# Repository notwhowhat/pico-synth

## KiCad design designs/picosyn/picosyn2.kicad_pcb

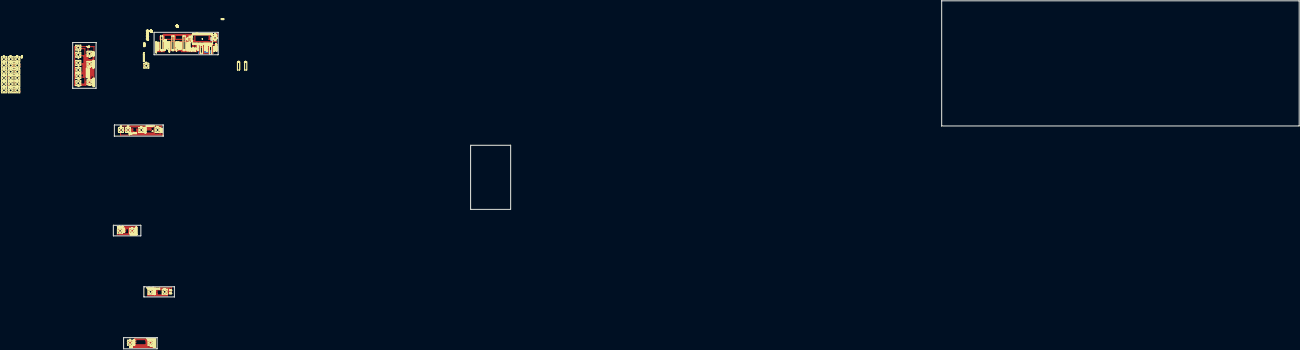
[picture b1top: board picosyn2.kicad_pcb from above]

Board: 2 copper layers, 170 parts (0 on the bottom side), 190 nets.

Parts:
C1: 100 nF; CP_Radial_D5.0mm_P2.50mm
C2: 47 µF; CP_Radial_D5.0mm_P2.50mm
C3, C4, C5, C6, C7, C8, C9: C; CP_Radial_D5.0mm_P2.50mm
D1: 1N4148; D_DO-35_SOD27_P7.62mm_Horizontal
D2, D3, D4, D5, D19, D20, D21, D22, D23, D24, D25, D26, D27, D28, D29, D30, D31, D32, D33, D34, D35, D36, D37, D38, D39, D40, D41, D43, D44, D45, D46, D47, D48, D49, D50, D51: LED; LED_D3.0mm
J3, J6, J9, J11, J15, J31, J32, J34, J35: Conn_01x02_Pin; PinHeader_1x02_P2.54mm_Vertical
J4: BUTTONS_A; PinHeader_1x09_P2.54mm_Vertical
J5: LEDS_A; PinHeader_1x10_P2.54mm_Vertical
J7: BUTTONS_B; PinHeader_1x04_P2.54mm_Vertical
J8, J27: LEDS_B; PinHeader_1x07_P2.54mm_Vertical
J10, J24: LEDS_C; PinSocket_1x06_P2.54mm_Vertical
J12: BUTTONS_C; PinHeader_1x02_P2.54mm_Vertical
J13: BUTTONS_D; PinHeader_1x02_P2.54mm_Vertical
J14: LEDS_D; PinSocket_1x05_P2.54mm_Vertical
J16, J22: BUTTONS_E; PinHeader_1x02_P2.54mm_Vertical
J17, J28: LEDS_E; PinHeader_1x07_P2.54mm_Vertical
J18: BUTTONS_A; PinSocket_1x09_P2.54mm_Vertical
J19: BUTTONS_D; PinSocket_1x02_P2.54mm_Vertical
J20: BUTTONS_C; PinSocket_1x02_P2.54mm_Vertical
J21: BUTTONS_B; PinSocket_1x04_P2.54mm_Vertical
J23: LEDS_A; PinSocket_1x10_P2.54mm_Vertical
J25: Conn_01x05_Pin; PinSocket_1x05_P2.54mm_Vertical
J26: POTS_B; PinHeader_1x08_P2.54mm_Vertical
J30, J33: Conn_01x04_Pin; PinHeader_1x04_P2.54mm_Vertical
R1, R3, R6, R7, R8, R9, R10, R12, R13, R14, R15, R16, R17, R18, R19, R20, R21, R22, R23, R24, R25, R26, R27, R28, R29, R30, R31, R32, R33, R34, R35, R36, R37, R38, R39, R40, R41, R42, R43, R44: R_US; R_Axial_DIN0204_L3.6mm_D1.6mm_P5.08mm_Horizontal
R2: 220; R_Axial_DIN0204_L3.6mm_D1.6mm_P5.08mm_Horizontal
R4: 1k8; R_Axial_DIN0204_L3.6mm_D1.6mm_P5.08mm_Horizontal
R5: 100; R_Axial_DIN0204_L3.6mm_D1.6mm_P5.08mm_Horizontal
R11: 2k2; R_Axial_DIN0204_L3.6mm_D1.6mm_P5.08mm_Horizontal
SW1, SW3, SW4, SW5, SW6, SW7, SW8, SW9, SW10, SW11, SW12, SW13, SW14, SW15, SW16, SW17, SW18, SW19, SW20, SW21, SW34, SW35, SW36, SW37, SW38, SW39, SW40, SW41, SW42, SW43, SW44, SW45, SW46, SW47, SW48, SW49, SW50, SW51: SW_Push; SW_PUSH-12mm
U1: H11L1; DIP-6_W7.62mm
U2, U11, U15: MCP23017_SP; DIP-28_W7.62mm
U3: Pico; RPi_Pico_SMD_TH
U4, U12, U13, U14: 74HC4051; DIP-16_W7.62mm
U8: 24LC256; DIP-8_W7.62mm

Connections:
+3.3V: C4.2, C6.2, C7.1, C8.2, C9.2, R1.2, R11.2, SW3.2, SW4.2, SW5.2, SW6.2, SW7.2, SW8.2, SW9.2, SW10.2, SW11.2, SW12.2, SW13.2, SW14.2, SW15.2, SW16.2, SW17.2, SW18.2, SW19.2, SW20.2, SW21.2, U1.6, U2.9 (VDD), U4.16 (VCC), U8.8 (VCC), U11.9 (VDD), U12.16 (VCC), U13.16 (VCC), U14.16 (VCC), U15.9 (VDD)
AUDIO: R2.1, U3.1 (GPIO0)
B1: R42.1, U3.16 (GPIO12)
B2: J22.1, R43.1, U3.15 (GPIO11)
B3: J22.2, R44.1, U3.14 (GPIO10)
GND: C1.2, C3.1, C4.1, C5.1, C6.1, C7.2, C8.1, C9.1, R4.1, R5.1, U1.5, U2.10 (VSS), U2.15 (A0), U2.16 (A1), U2.17 (A2), U2.18 (~RESET), U3.42 (GND), U4.6 (~E), U4.8 (GND), U8.1 (A0), U8.2 (A1), U8.3 (A2), U8.4 (GND), U8.7 (WP), U11.10 (VSS), U11.15 (A0), U11.16 (A1), U11.17 (A2), U11.18 (~RESET), U12.6 (~E), U12.8 (GND), U13.6 (~E), U13.7 (VEE), U13.8 (GND), U14.6 (~E), U14.7 (VEE), U14.8 (GND), U15.10 (VSS), U15.15 (A0), U15.16 (A1), U15.17 (A2), U15.18 (~RESET)
IO_EXP_INT_BA: U11.19 (INTB), U11.20 (INTA)
L1: J25.1, U3.20 (GPIO15)
L2: J25.2, U3.19 (GPIO14)
L3: J25.3, U3.17 (GPIO13)
MIDI: R1.1, U1.4, U3.2 (GPIO1)
MUX_A: U3.31 (GPIO26_ADC0), U12.3 (A)
MUX_B: U3.32 (GPIO27_ADC1), U4.3 (A), U13.3 (A)
MUX_C: U3.34 (GPIO28_ADC2), U14.3 (A)
MUX_S0: U3.29 (GPIO22), U4.11 (S0), U12.11 (S0), U13.11 (S0), U14.11 (S0)
MUX_S1: U3.27 (GPIO21), U4.10 (S1), U12.10 (S1), U13.10 (S1), U14.10 (S1)
MUX_S2: U3.26 (GPIO20), U4.9 (S2), U12.9 (S2), U13.9 (S2), U14.9 (S2)
unnamed: C1.1, C2.1, R2.2, R5.2
unnamed: C2.2, R4.2
unnamed: D1.2 (A), U1.1
unnamed: D1.1 (K), R3.1, U1.2
unnamed: D2.2 (A), D22.2 (A), D34.2 (A), D35.2 (A), D36.2 (A), D37.2 (A), D38.2 (A), D39.2 (A), D40.2 (A), D41.2 (A), J3.2
unnamed: D2.1 (K), R6.2
unnamed: D3.2 (A), D4.2 (A), D5.2 (A), D43.2 (A), D44.2 (A), J11.2
unnamed: D3.1 (K), R12.2
unnamed: D4.1 (K), R31.2
unnamed: D5.1 (K), R32.2
unnamed: D19.2 (A), D20.2 (A), D21.2 (A), D23.2 (A), D24.2 (A), D25.2 (A), D26.2 (A), J6.2
unnamed: D19.1 (K), R18.2
unnamed: D20.1 (K), R19.2
unnamed: D21.1 (K), R20.2
unnamed: D22.1 (K), R7.2
unnamed: D23.1 (K), R21.2
unnamed: D24.1 (K), R22.2
unnamed: D25.1 (K), R23.2
unnamed: D26.1 (K), R24.2
unnamed: D27.2 (A), D28.2 (A), D29.2 (A), D30.2 (A), D31.2 (A), D32.2 (A), D33.2 (A), J9.2
unnamed: D27.1 (K), R25.2
unnamed: D28.1 (K), R26.2
unnamed: D29.1 (K), R27.2
unnamed: D30.1 (K), R28.2
unnamed: D31.1 (K), R29.2
unnamed: D32.1 (K), R30.2
unnamed: D34.1 (K), R8.2
unnamed: D35.1 (K), R9.2
unnamed: D36.1 (K), R10.2
unnamed: D37.1 (K), R13.2
unnamed: D38.1 (K), R14.2
unnamed: D39.1 (K), R15.2
unnamed: D40.1 (K), R16.2
unnamed: D41.1 (K), R17.2
unnamed: D43.1 (K), R33.2
unnamed: D44.1 (K), R34.2
unnamed: D45.2 (A), D46.2 (A), D47.2 (A), D48.2 (A), D49.2 (A), D50.2 (A), D51.2 (A), J15.2
unnamed: D45.1 (K), R35.2
unnamed: D46.1 (K), R36.2
unnamed: D47.1 (K), R37.2
unnamed: D48.1 (K), R38.2
unnamed: D49.1 (K), R39.2
unnamed: D50.1 (K), R40.2
unnamed: D51.1 (K), R41.2
unnamed: J3.1, SW1.2, SW34.2, SW35.2, SW36.2, SW37.2, SW38.2, SW39.2, SW40.2, SW41.2
unnamed: J4.1, SW41.1
unnamed: J4.2, SW40.1
unnamed: J4.3, SW39.1
unnamed: J4.4, SW38.1
unnamed: J4.5, SW37.1
unnamed: J4.6, SW36.1
unnamed: J4.7, SW35.1
unnamed: J4.8, SW34.1
unnamed: J4.9, SW1.1
unnamed: J5.1, R17.1
unnamed: J5.2, R16.1
unnamed: J5.3, R15.1
unnamed: J5.4, R14.1
unnamed: J5.5, R13.1
unnamed: J5.6, R10.1
unnamed: J5.7, R9.1
unnamed: J5.8, R8.1
unnamed: J5.9, R7.1
unnamed: J5.10, R6.1
unnamed: J6.1, SW42.2, SW43.2, SW44.2, SW45.2
unnamed: J7.1, SW42.1
unnamed: J7.2, SW43.1
unnamed: J7.3, SW44.1
unnamed: J7.4, SW45.1
unnamed: J8.1, R24.1
unnamed: J8.2, R23.1
unnamed: J8.3, R22.1
unnamed: J8.4, R21.1
unnamed: J8.5, R20.1
unnamed: J8.6, R19.1
unnamed: J8.7, R18.1
unnamed: J9.1, SW46.2, SW47.2
unnamed: J10.1, R30.1
unnamed: J10.2, R29.1
unnamed: J10.3, R28.1
unnamed: J10.4, R27.1
unnamed: J10.5, R26.1
unnamed: J10.6, R25.1
unnamed: J11.1, SW48.2, SW49.2
unnamed: J12.1, SW47.1
unnamed: J12.2, SW46.1
unnamed: J13.1, SW49.1
unnamed: J13.2, SW48.1
unnamed: J14.1, R32.1
unnamed: J14.2, R31.1
unnamed: J14.3, R12.1
unnamed: J14.4, R34.1
unnamed: J14.5, R33.1
unnamed: J15.1, SW50.2, SW51.2
unnamed: J16.1, SW51.1
unnamed: J16.2, SW50.1
unnamed: J17.1, R41.1
unnamed: J17.2, R40.1
unnamed: J17.3, R39.1
unnamed: J17.4, R38.1
unnamed: J17.5, R37.1
unnamed: J17.6, R36.1
unnamed: J17.7, R35.1
unnamed: J18.1, U11.8 (GPB7)
unnamed: J18.2, U11.7 (GPB6)
unnamed: J18.3, U11.6 (GPB5)
unnamed: J18.4, U11.5 (GPB4)
unnamed: J18.5, U11.4 (GPB3)
unnamed: J18.6, U11.3 (GPB2)
unnamed: J18.7, U11.2 (GPB1)
unnamed: J18.8, U11.1 (GPB0)
unnamed: J18.9, R42.2
unnamed: J19.1, U11.28 (GPA7)
unnamed: J19.2, U11.27 (GPA6)
unnamed: J20.1, U11.26 (GPA5)
unnamed: J20.2, U11.25 (GPA4)
unnamed: J21.1, U11.24 (GPA3)
unnamed: J21.2, U11.23 (GPA2)
unnamed: J21.3, U11.22 (GPA1)
unnamed: J21.4, U11.21 (GPA0)
unnamed: J23.1, U15.22 (GPA1)
unnamed: J23.2, U15.21 (GPA0)
unnamed: J23.3, U15.8 (GPB7)
unnamed: J23.4, U15.7 (GPB6)
unnamed: J23.5, U15.6 (GPB5)
unnamed: J23.6, U15.5 (GPB4)
unnamed: J23.7, U15.4 (GPB3)
unnamed: J23.8, U15.3 (GPB2)
unnamed: J23.9, U15.2 (GPB1)
unnamed: J23.10, U15.1 (GPB0)
unnamed: J24.1, U15.28 (GPA7)
unnamed: J24.2, U15.27 (GPA6)
unnamed: J24.3, U15.26 (GPA5)
unnamed: J24.4, U15.25 (GPA4)
unnamed: J24.5, U15.24 (GPA3)
unnamed: J24.6, U15.23 (GPA2)
unnamed: J25.4, U2.28 (GPA7)
unnamed: J25.5, U2.27 (GPA6)
unnamed: J27.1, U2.7 (GPB6)
unnamed: J27.2, U2.6 (GPB5)
unnamed: J27.3, U2.5 (GPB4)
unnamed: J27.4, U2.4 (GPB3)
unnamed: J27.5, U2.3 (GPB2)
unnamed: J27.6, U2.2 (GPB1)
unnamed: J27.7, U2.1 (GPB0)
unnamed: J28.1, U2.26 (GPA5)
unnamed: J28.2, U2.25 (GPA4)
unnamed: J28.3, U2.24 (GPA3)
unnamed: J28.4, U2.23 (GPA2)
unnamed: J28.5, U2.22 (GPA1)
unnamed: J28.6, U2.21 (GPA0)
unnamed: J28.7, U2.8 (GPB7)
unnamed: J30.1, U12.12 (A3)
unnamed: J30.2, U12.15 (A2)
unnamed: J30.3, U12.14 (A1)
unnamed: J30.4, U12.13 (A0)
unnamed: J31.1, U12.5 (A5)
unnamed: J31.2, U12.1 (A4)
unnamed: J32.1, U12.4 (A7)
unnamed: J32.2, U12.2 (A6)
unnamed: J33.1, U4.12 (A3)
unnamed: J33.2, U4.15 (A2)
unnamed: J33.3, U4.14 (A1)
unnamed: J33.4, U4.13 (A0)
unnamed: J34.1, U4.5 (A5)
unnamed: J34.2, U4.1 (A4)
unnamed: J35.1, U4.4 (A7)
unnamed: J35.2, U4.2 (A6)
unnamed: C5.2, U4.7 (VEE)
unnamed: C3.2, U12.7 (VEE)
SCK: U2.12 (SCK), U15.12 (SCK)
SCL: U3.5 (GPIO3), U8.6 (SCL), U11.12 (SCK)
SDA: R11.1, U2.13 (SDA), U3.4 (GPIO2), U8.5 (SDA), U11.13 (SDA), U15.13 (SDA)

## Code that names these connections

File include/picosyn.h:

#include <stdbool.h>
#include <stddef.h>
#include <stdint.h>

#ifndef PICOSYN_H
#define PICOSYN_H

#define ERR_LED_PIN 25
#define MIDI_LED_PIN 15
#define AUDIO_PIN 2

#define IO_EXPANDER_INT_PIN 23
#define MUX_A_PIN 17
#define MUX_B_PIN 19
#define MUX_C_PIN 20

#define VOICE_COUNT 8
#define GAIN 10//8192 // 2^(16-3)

#define SAMPLE_RATE 44100

typedef int32_t fixed;
#define FIXED_MAX INT32_MAX
#define FIXED_MIN INT32_MIN

static inline fixed mul_fixed(fixed a, fixed b) {
    int64_t tmp = ((int64_t)a * (int64_t) b);
    return (fixed)(tmp >> 31);
}
static inline fixed div_fixed(fixed a, fixed b) {
    int64_t tmp = (int64_t)(a << 31);
    return (fixed)(tmp / b);
}
static inline fixed float_to_fixed(float x) {
    // float should be between -1.0 and 1.0
    return (fixed)(x * FIXED_MAX);
}
static inline float fixed_to_float(fixed x) {
    // float will be between -1.0 and 1.0
    return ((float)x / FIXED_MAX);
}
static inline fixed byte_to_fixed(uint8_t x) {
    // scales so value is centered around 0ish.
    return (int64_t)x * 16843009 - FIXED_MAX;
}
static inline int sign(int x) {
    return (x > 0) - (x < 0);
}


// fixed type is used to avoid incorrect usage. it is a decimal type with one sign bit 
// and 31 fractional bits, i.e q31
// the fixed type should be used to represent fractions between -1.0 and 1.0

// rpi pico is little endian


/*
features when all finished:

2x osc. for each:
- selectable waveforms: sin, tri, saw, square, noise
- changeable pitch !
- supersaw
- (pwm)
together (modutlation)
- sync
- ring mod
- fm (osc 1 will modulate osc 2. knob will change modifier)

2x lfo. for each:
- rate
- amount
- as many mod destinations as possible
- (sync to clock maybe)

3x env. for each:
- attack
- decay
- sustain
- release
- for amp, filter and general modulation
modulation:
- env amount (for mod and filter)
- as many sources as possible for mod env. same as lfo if possible

filter.
- selecatble variants: lowpass, highpass and bandpass
- cutoff 
- resonance
- (drive)
- (key tracking) !

arpeggiator.
- midi sync bpm or button
- hold
- up, down, random (converge and diverge)
- (gate)

legato 
portamento 

presets.

*/

float pot_mod;
float pot_divider;

#endif

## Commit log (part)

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2024-03-15 intitial commit
2024-03-16 all working for further developement
2024-03-19 working midi in kindof
2024-08-14 midi in is kindof working in a way, but notes are not triggered (the sound is just being turned on or off)
2024-08-16 you can now play notes, but the midi is a bit buggy because of my hacky monophony
2024-08-24 fixed some random horable midi bug. the voices don't really work now, but they will soon.
2024-09-15 voice system is done. but the program is slow. time to refactor
2024-09-21 i've actually got sound! the synth works quite well, you can play notes now, but the midi is a bit buggy because the note-off commands aren't always recieved.
2024-09-27 moved the pwm code out of main. will be run on second core.
2024-09-28 i refactored the midi/voice handeling code like crazy, and the bug still exists
2024-09-28 I ACTUALLY HAVE VOICES THAT KINDOF WORK IN A HALFBUGGY WAY!!!! they don't sound that great, probably because of the phases... or something else wacky!!
2024-10-11 i fixed the weird phaser-like isue. what was happening was that it was clipping over the max uint16 size
2024-10-11 added another type of voice stealing. instead of stealing the lowest note, it steals the oldest one. this is done so that if there would be long releases on the notes they wouldn't make a huge differ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
2024-10-27 added gitignore
2024-10-28 attack, decay and sustain phases work
2024-10-28 The envelope now works. Mostly. It gets a bit weird while playing chords. Probably because of performance
2024-10-31 fixed some small bugs. one big one remains: the pitch gets lowered when more than three notes are played simultainously. this is caused by poor performance. the function on_pwm_interrupt should take 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
2024-11-09 pushed up the clock speed. basically, the pitch gets lowered when the program has too much to do, and is too slow. i also refactored the sample-generating and broke it out into a function. the proble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
2024-11-22 refactored envelopes and changed the wavetable from semitones to cents
2024-11-29 changed the wavetable so that i have a table of increments instead of just frequencies. this is much quicker
2025-03-24 working on the prototype pannel and the multiplexers.
2025-06-25 added minor debug things. midi is now done in interrupts. will rewrite envelopes for easier controls
2025-07-04 added variable envelope times, though they don't really work. i have started to refactor and organize to make testing outisde of th pico possible
2025-08-31 reorganized the project to make local testing possible. maybe not perfect, but i guess it works. probably no progress since last commit. i'm not really sure.
2025-08-31 Delete build directory.
    I forgot to add it to .gitignore a while back.
2025-11-08 little progress on physical controlls, but most related to patching a bug and related testing. when the note was turned off, amp_env.mod turned negative, throwing the whole system off. this was cause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
2025-11-09 minor cleanup and prep for controls
2025-11-30 added lfo code but isn't implemented no audio output, so will backtrack to find problem
2025-11-30 fixed audio bug the note was set to 0 and the increment was set to the note, so no audio
2025-12-07 mostly notes
2025-12-07 implemented ring modulation and oscillator sync
2025-12-21 updated the filter
    the algorithm was changed to be more like the nord lead. i probably butchered it,
    but it sounds fine. keytracking has also been added. it hasn't been
    tested much, but it seems to work.
2026-01-02 Revert "updated the filter"
    This reverts commit 32d82a88e2dd79d0af9717b46c0244898cdf98f8.
2026-01-02 Revert "Revert "updated the filter""
    This reverts commit d3f87db82eb0bbd6ce517c49caa1e413069c27b9.
    i made a mistake
2026-01-06 added legato and mono portamento
    portamento does not work in poly mode, that's the next step.
    i fixed a minor bug which caused notes in mono mode to end when
    a key that has finished playing was released
2026-04-10 cleaned up code
    i also spilt it into more files for easier access. i think that's all.
    for hardware, it's a mess. i changed breadboards, but it turns out that
    the new one doesn't conduct electricity where it needs to. i will need
    to change it back. that is the main reason for it not working. i think.
2026-05-06 cleanup, improved debug, and fixed point
    i have only just started with the fixed point math
2026-05-07 improved test interface
    made it possible to test locally and plot the results.
    a function in tests.c exports test data as plot.csv (i could have
    probably come up with a better name). the same source file runs the
    script, which plots the data using matplotlib
2026-05-26 rewrote oscilator code to use fixed point
    next step is to do the same with lfos
2026-05-26 rewrote lfo code to use fixed point too
2026-06-09 made it possible to have linear and exponential envelope generators
2026-06-09 cleaned up envelope code. sholud be ready for integer math
2026-06-15 fixed a bug resulting in the square wave always being negative
    also started working on testing the filter and later converting it to
    use fixed point arithmetic
2026-06-23 implemented all io expander code
    this has not been tested because a lack of hardware.
    some code has also been cleaned up, and functions have been renamed.
2026-06-24 wrote all preset and muxing code
    the code has not been tested. it really should be though.
